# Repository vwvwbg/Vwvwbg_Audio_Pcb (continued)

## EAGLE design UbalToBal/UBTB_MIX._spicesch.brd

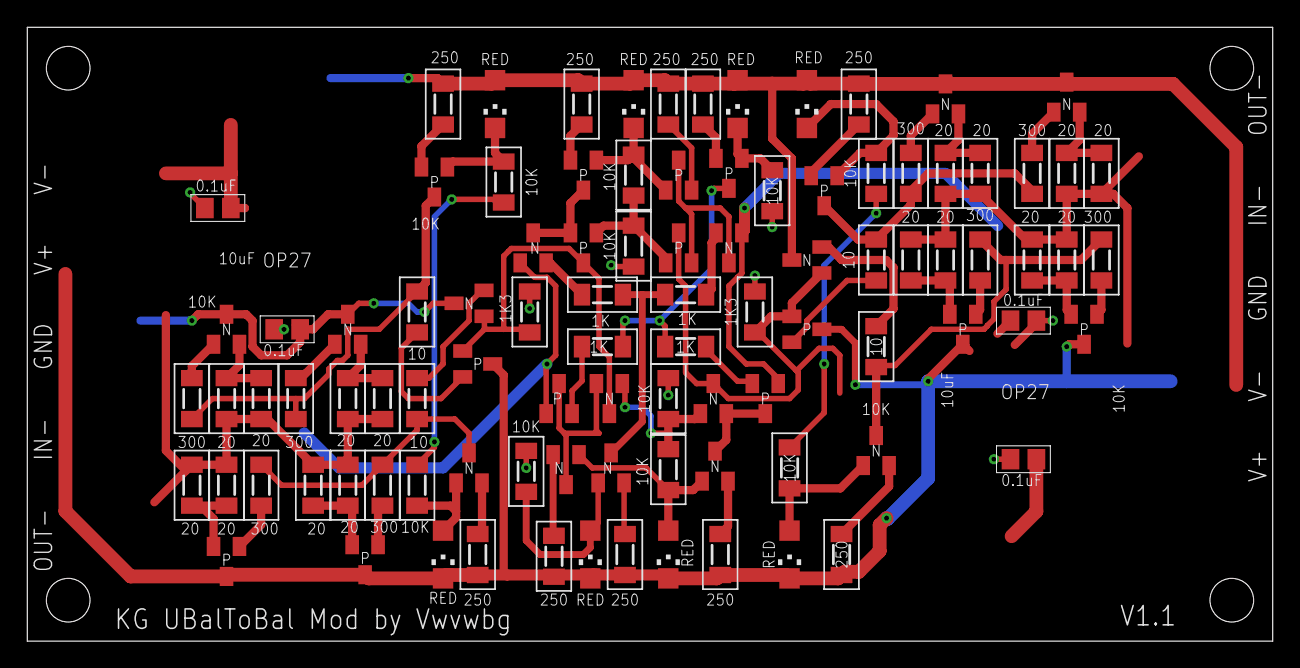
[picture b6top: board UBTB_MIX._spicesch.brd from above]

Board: 2 copper layers, 91.3 x 45.0 mm, 96 parts (0 on the bottom side), 65 nets.

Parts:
C2, C3, C5, C6: 0.0001; C0805
LED1, LED2, LED3, LED4, LED5, LED6, LED7, LED8: CHIPLED_1206
Q1, Q3, Q5, Q8, Q9, Q11, Q13, Q14: 2SC3324; TRANSISTOR_SOT23-BEC
Q2, Q4, Q6, Q7, Q10, Q12, Q15, Q16: 2SA1312; TRANSISTOR_SOT23-BEC
Q26, Q30, Q31, Q32, Q37, Q38, Q39: 2SC3324; SOT23
Q29, Q33, Q34, Q35, Q36, Q40, Q41: 2SA1312; SOT23-BEC
R1, R2, R15, R18, R22, R23, R35, R36, R43, R44: 250; MINI_MELF-0204W
R3, R4, R19, R20, R29, R32, R33, R34, R45, R46: 10K; MINI_MELF-0204W
R5, R6, R21, R24: 10; MINI_MELF-0204W
R7, R8, R9, R10, R25, R26, R27, R28: 300; MINI_MELF-0204W
R11, R12, R13, R14, R30, R31, R47, R49, R50, R52, R53, R54, R55, R56, R57, R58: 20; MINI_MELF-0204W
R37, R38: 1K3; MINI_MELF-0204W
R39, R40, R41, R42: 1K; MINI_MELF-0204W

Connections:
BOUT+: R11.1, R12.2, R13.1, R14.2, R50.1, R52.1, R53.2, R54.2
BOUT-: R30.1, R31.2, R47.1, R49.2, R55.1, R56.1, R57.2, R58.2
GND: C2.1, C3.2, C5.1, C6.2, R32.2, R33.1, R37.1, R38.1, R45.1, R46.2
IN+: Q35.B, Q39.1
IN-: Q34.B, Q38.1
unnamed: Q2.E, R5.2
unnamed: Q3.E, R2.2
unnamed: Q4.E, R1.1
unnamed: LED5.C, Q4.B, R3.2
unnamed: LED6.A, Q3.B, R4.1
unnamed: Q4.C, R5.1, R7.2, R10.2
unnamed: Q3.C, R6.2, R8.1, R9.1
unnamed: Q1.E, R6.1
unnamed: R3.1, R4.2
unnamed: Q5.B, R7.1
unnamed: Q5.E, R11.2, R50.2
unnamed: Q7.B, R9.2
unnamed: Q8.B, R10.1
unnamed: Q6.B, R8.2
unnamed: Q6.E, R12.1, R53.1
unnamed: Q8.E, R13.2, R52.2
unnamed: Q7.E, R14.1, R54.1
unnamed: Q11.E, R18.2
unnamed: Q12.E, R15.1
unnamed: LED7.C, Q12.B, R19.2
unnamed: LED8.A, Q11.B, R20.1
unnamed: Q12.C, R21.1, R25.2, R28.2
unnamed: Q11.C, R24.2, R26.1, R27.1
unnamed: Q10.E, R21.2
unnamed: Q9.E, R24.1
unnamed: R19.1, R20.2
unnamed: Q13.B, R25.1
unnamed: Q15.B, R26.2
unnamed: Q14.B, R28.1
unnamed: Q16.B, R27.2
unnamed: Q13.E, R30.2, R55.2
unnamed: Q15.E, R31.1, R58.1
unnamed: Q14.E, R47.2, R56.2
unnamed: Q16.E, R49.1, R57.1
unnamed: Q30.2, R22.2
unnamed: Q31.2, R23.2
unnamed: Q31.3, Q32.2, Q34.C
unnamed: Q30.3, Q35.C, Q37.2
unnamed: LED1.A, Q30.1, Q31.1, R29.1
unnamed: Q32.1, Q37.1, R29.2, R32.1
unnamed: Q33.B, Q41.B, R33.2, R34.1
unnamed: Q29.C, Q33.E, Q39.3
unnamed: LED2.C, Q29.B, Q40.B, R34.2
unnamed: Q38.3, Q40.C, Q41.E
unnamed: Q29.E, R35.1
unnamed: Q40.E, R36.1
unnamed: LED3.C, Q36.B, R45.2
unnamed: Q36.E, R43.1
unnamed: Q36.C, R41.2, R42.2
unnamed: Q34.E, R42.1
unnamed: Q35.E, R41.1
unnamed: Q39.2, R39.2
unnamed: Q38.2, R40.2
unnamed: Q26.3, R39.1, R40.1
unnamed: Q26.2, R44.2
unnamed: LED4.A, Q26.1, R46.1
UOUT+: Q1.B, Q2.B, Q33.C, Q37.3, R37.2
UOUT-: Q9.B, Q10.B, Q32.3, Q41.C, R38.2
V+: C2.2, C5.2, LED2.A, LED3.A, LED5.A, LED7.A, Q1.C, Q5.C, Q8.C, Q9.C, Q13.C, Q14.C, R1.2, R15.2, R35.2, R36.2, R43.2
V-: C3.1, C6.1, LED1.C, LED4.C, LED6.C, LED8.C, Q2.C, Q6.C, Q7.C, Q10.C, Q15.C, Q16.C, R2.1, R18.1, R22.1, R23.1, R44.1
